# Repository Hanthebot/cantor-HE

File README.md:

# cantor-HE
42 key column staggered split, now with hall effect (WIP)

> Warning! The hardware should work fine, but firmware was not verified yet due to flashing issue.

Hall-effect variant of [Cantor](https://github.com/diepala/cantor), a 42-key split keyboard.

Wooting compatible, reversible, qmk/vial support, and sharing PCB dimension with official Cantor

Firmware / schematics based on [TrueStrike42](https://github.com/byungyoonc/TrueStrike42)

## Preparation

### Board
| Component            | Qty |
| -------------------- | --- |
| PCB                  | 2   |
| SOT-23 SS49E         | 42  |
| SOIC-16 74HC4051(D)  | 6   |
| 0805 0.1uf capacitor | 48  |
| PJ320A TRRS socket   | 2   |
| Blackpill MCU        | 2   |
- For capacitor, 0.1~1uf should be fine
- And obviously, USB-C cable of your choice (with machine) and TRS/TRRS cable of your choice

### Case
- Option A: 3D printed case (I bet you can find one for Cantor)
- Option B: Cheap plate cut
  - requires heat insert and standoff
  - 3T mdf panel of A4 size can fit 2x top & bottom plate
      - and costs about $1
  - plate file provided in this repo
- I do not think original barebone design will work well, as switches are not soldered / mechanically connected.

| Component                  | Qty |
| -------------------------- | --- |
| M2 screw 6mm               | 12  |
| M2 heat insert 3*3         | 12  |
| M2 standoff 7mm + 3mm head | 12  |
- Flathead screw was used
- Standoff can be shorter or longer - but I recommend 5mm at least

### Switches
| Component                          | Qty |
| ---------------------------------- | --- |
| Wooting compatible magnetic switch | 42  |
- While those without side pins should be fine, I'd use one with side pins so that they fix better
- Firmware fix may be required to use the opposite polarity

## [Build guide](GUIDE.md)
WIP. You may check images folder / [Boardloaf-HE's build guide](https://github.com/Hanthebot/Boardloaf-HE/blob/main/GUIDE.md). 

\+ jump back for side detection, firmware is shared between halves

Almost the only difference is that you can solder SOIC-16 multiplexor on either side, preferably at the back of the keyboard.

## Features
- Supports both APC and rapid trigger
- Cheap, simple, and working
- 3 multiplexor on each side, scanning 7 keys per mux

## Changes from Boardloaf-HE
- full duplex communication
- reversible SOIC-16 footprint
- except that, firmware remains largely identical.
- STM32F4x1 MCU, so key precision is expected to have been improved by ~= 10x

## Remarks
- Initial config recommendation: 30% / 20% / 20% / 10% / 10% / 20% (APC act / release; RT init dead / act offset / release offset / bottom dead)
- More documentation: to be done
- Case
  - if your case works for official Cantor, it must work for this
- Random
  - PCB schematics are almost directly from TrueStrike42

## Sponsorship
PCB was generously sponsored by [PCBWay](https://www.pcbway.com/)! Their PCB was indeed of high quality. I did not go with options like matte coating or ENIG, but the board was generally better.

Apart from their great quality, what I felt different was their customer service. There were real human involved in production / communication process and you could feel that they want to help you. In the world filled by chatbot / hallucination, such experience is very rare indeed.

If you are designing a PCB & want some human to check it beforehand, I think PCBWay is superb. They will save you trial and errors.

## Licenses
All code under firmware folder, along with HW, follows GPL v3.
- inherited from TrueStrike42 / Cantor respectively.
- reversible SOT23 / SOIC-16 footprint can be used with MIT.

Webapp follows MIT license.

## Disclaimer
Webapp and firmware (modification) were vibe coded.

Firmware needs future check.

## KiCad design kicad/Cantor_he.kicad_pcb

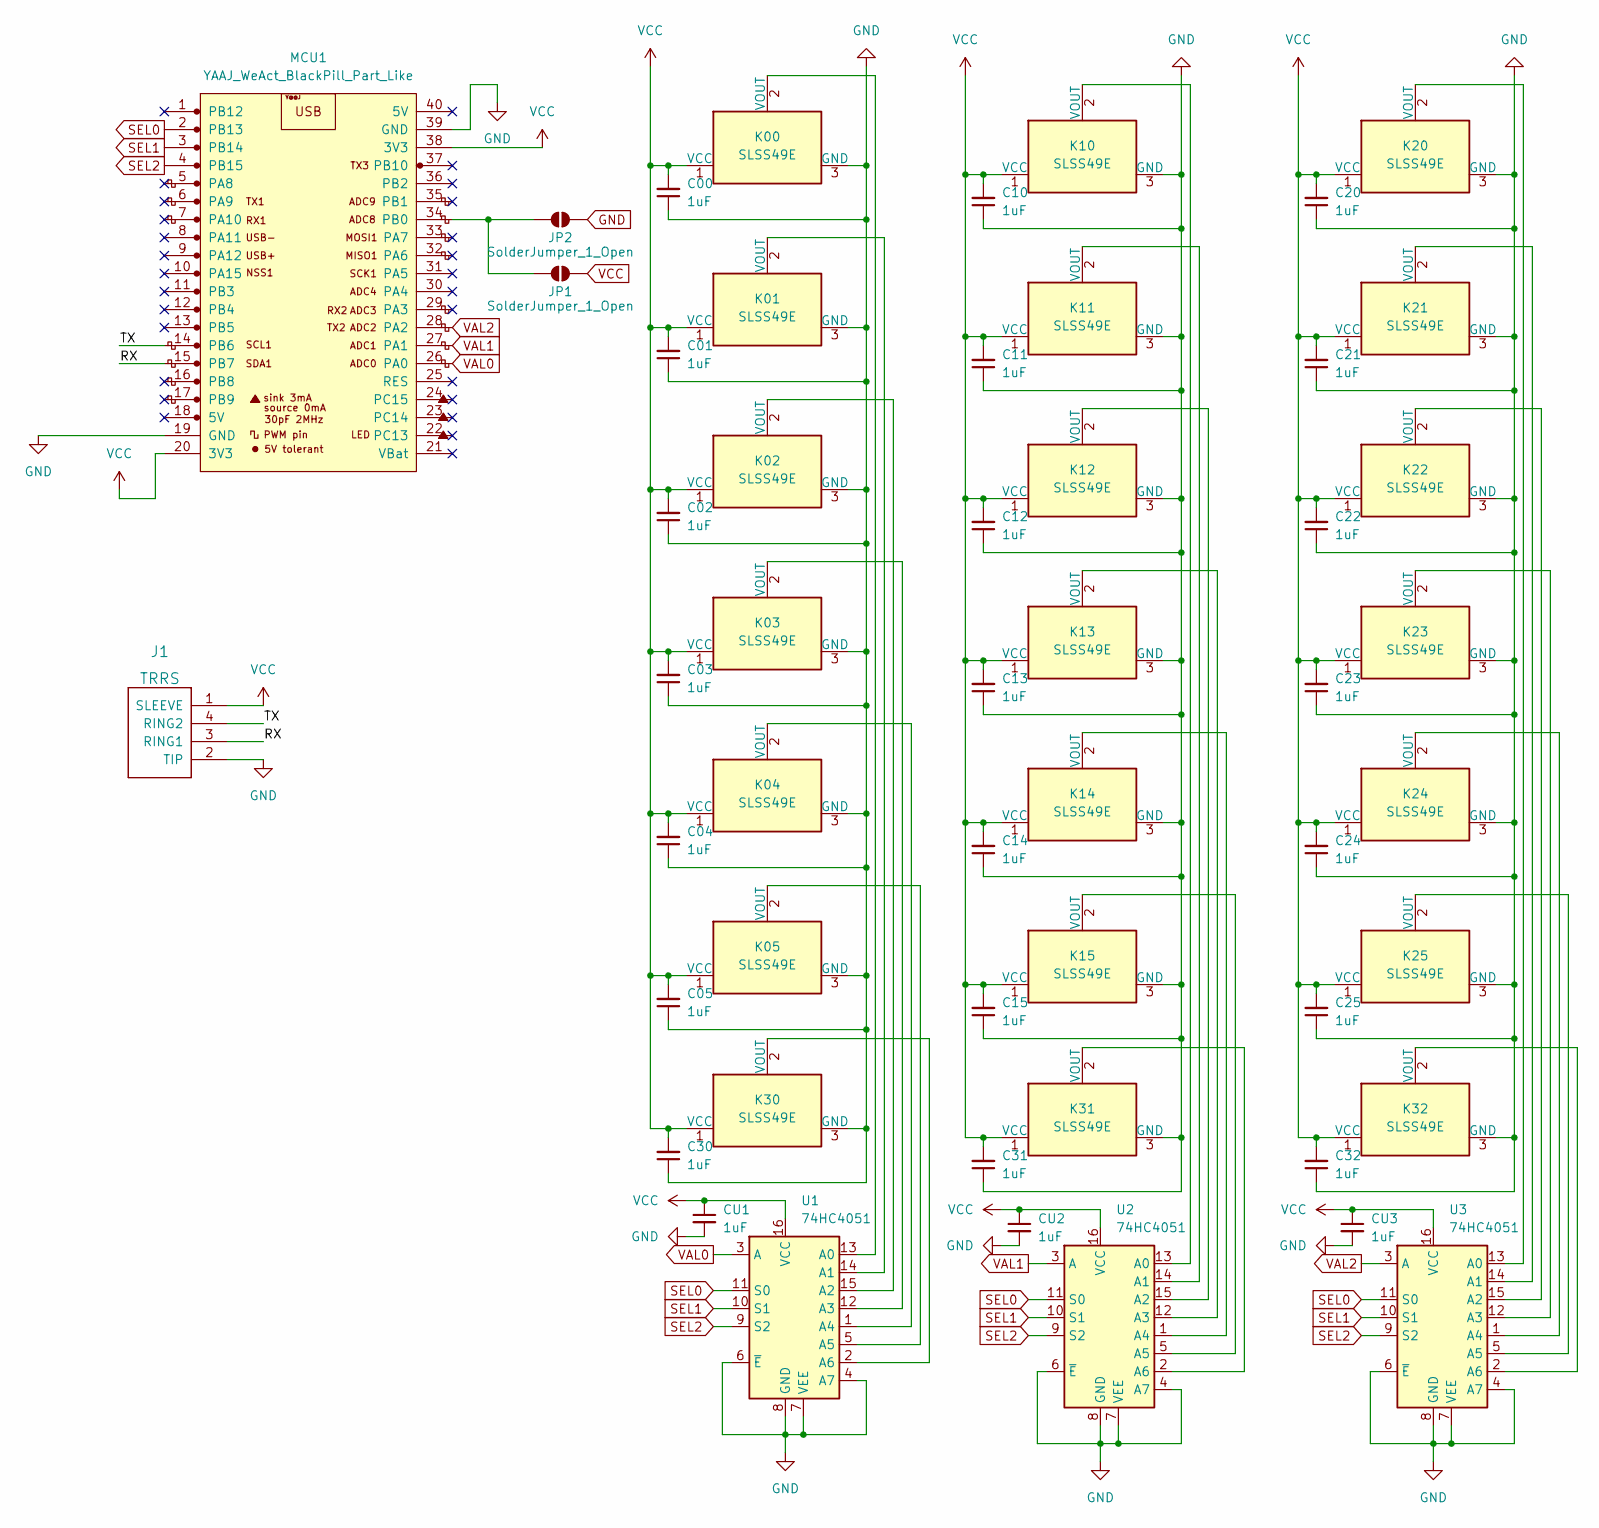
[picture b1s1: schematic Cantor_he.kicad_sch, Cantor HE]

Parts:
C00, C01, C02, C03, C04, C05, C10, C11, C12, C13, C14, C15, C20, C21, C22, C23, C24, C25, C30, C31, C32: 1uF; C_0805_2012Metric_Pad1.18x1.45mm_HandSolder
CU1, CU2, CU3: 1uF; C_0805_2012Metric_Pad1.18x1.45mm_HandSolder
J1: TRRS; MJ-4PP-9_Cantor_MX_TX-RX_Crossover
JP1, JP2: SolderJumper_1_Open; SolderJumper-2_P1.3mm_Open_TrianglePad1.0x1.5mm
K00, K01, K02, K03, K04, K05, K10, K11, K12, K13, K14, K15, K20, K21, K22, K23, K24, K25, K30, K31, K32: SLSS49E; HE-Switch-1U
MCU1: YAAJ_WeAct_BlackPill_Part_Like; Cantor_DS_YAAJ_WeAct_BlackPill_2
U1, U2, U3: 74HC4051; reversible-SOIC-16_3.9x9.9mm_P1.27mm

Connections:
/RX: J1.3 (RING1), MCU1.15 (PB7)
/TX: J1.4 (RING2), MCU1.14 (PB6)
GND: C00.1, C01.1, C02.1, C03.1, C04.1, C05.1, C10.1, C11.1, C12.1, C13.1, C14.1, C15.1, C20.1, C21.1, C22.1, C23.1, C24.1, C25.1, C30.1, C31.1, C32.1, CU1.2, CU2.2, CU3.2, J1.2 (TIP), JP2.2 (B), K00.3 (GND), K01.3 (GND), K02.3 (GND), K03.3 (GND), K04.3 (GND), K05.3 (GND), K10.3 (GND), K11.3 (GND), K12.3 (GND), K13.3 (GND), K14.3 (GND), K15.3 (GND), K20.3 (GND), K21.3 (GND), K22.3 (GND), K23.3 (GND), K24.3 (GND), K25.3 (GND), K30.3 (GND), K31.3 (GND), K32.3 (GND), MCU1.19 (GND), MCU1.39 (GND), U1.4 (A7), U1.6 (~E), U1.7 (VEE), U1.8 (GND), U2.4 (A7), U2.6 (~E), U2.7 (VEE), U2.8 (GND), U3.4 (A7), U3.6 (~E), U3.7 (VEE), U3.8 (GND)
unnamed: JP1.1 (A), JP2.1 (A), MCU1.34 (PB0)
unnamed: K00.2 (VOUT), U1.13 (A0)
unnamed: K01.2 (VOUT), U1.14 (A1)
unnamed: K02.2 (VOUT), U1.15 (A2)
unnamed: K03.2 (VOUT), U1.12 (A3)
unnamed: K04.2 (VOUT), U1.1 (A4)
unnamed: K05.2 (VOUT), U1.5 (A5)
unnamed: K10.2 (VOUT), U2.13 (A0)
unnamed: K11.2 (VOUT), U2.14 (A1)
unnamed: K12.2 (VOUT), U2.15 (A2)
unnamed: K13.2 (VOUT), U2.12 (A3)
unnamed: K14.2 (VOUT), U2.1 (A4)
unnamed: K15.2 (VOUT), U2.5 (A5)
unnamed: K20.2 (VOUT), U3.13 (A0)
unnamed: K21.2 (VOUT), U3.14 (A1)
unnamed: K22.2 (VOUT), U3.15 (A2)
unnamed: K23.2 (VOUT), U3.12 (A3)
unnamed: K24.2 (VOUT), U3.1 (A4)
unnamed: K25.2 (VOUT), U3.5 (A5)
unnamed: K30.2 (VOUT), U1.2 (A6)
unnamed: K31.2 (VOUT), U2.2 (A6)
unnamed: K32.2 (VOUT), U3.2 (A6)
SEL0: MCU1.2 (PB13), U1.11 (S0), U2.11 (S0), U3.11 (S0)
SEL1: MCU1.3 (PB14), U1.10 (S1), U2.10 (S1), U3.10 (S1)
SEL2: MCU1.4 (PB15), U1.9 (S2), U2.9 (S2), U3.9 (S2)
VAL0: MCU1.26 (PA0), U1.3 (A)
VAL1: MCU1.27 (PA1), U2.3 (A)
VAL2: MCU1.28 (PA2), U3.3 (A)
VCC: C00.2, C01.2, C02.2, C03.2, C04.2, C05.2, C10.2, C11.2, C12.2, C13.2, C14.2, C15.2, C20.2, C21.2, C22.2, C23.2, C24.2, C25.2, C30.2, C31.2, C32.2, CU1.1, CU2.1, CU3.1, J1.1 (SLEEVE), JP1.2 (B), K00.1 (VCC), K01.1 (VCC), K02.1 (VCC), K03.1 (VCC), K04.1 (VCC), K05.1 (VCC), K10.1 (VCC), K11.1 (VCC), K12.1 (VCC), K13.1 (VCC), K14.1 (VCC), K15.1 (VCC), K20.1 (VCC), K21.1 (VCC), K22.1 (VCC), K23.1 (VCC), K24.1 (VCC), K25.1 (VCC), K30.1 (VCC), K31.1 (VCC), K32.1 (VCC), MCU1.20 (3V3), MCU1.38 (3V3), U1.16 (VCC), U2.16 (VCC), U3.16 (VCC)

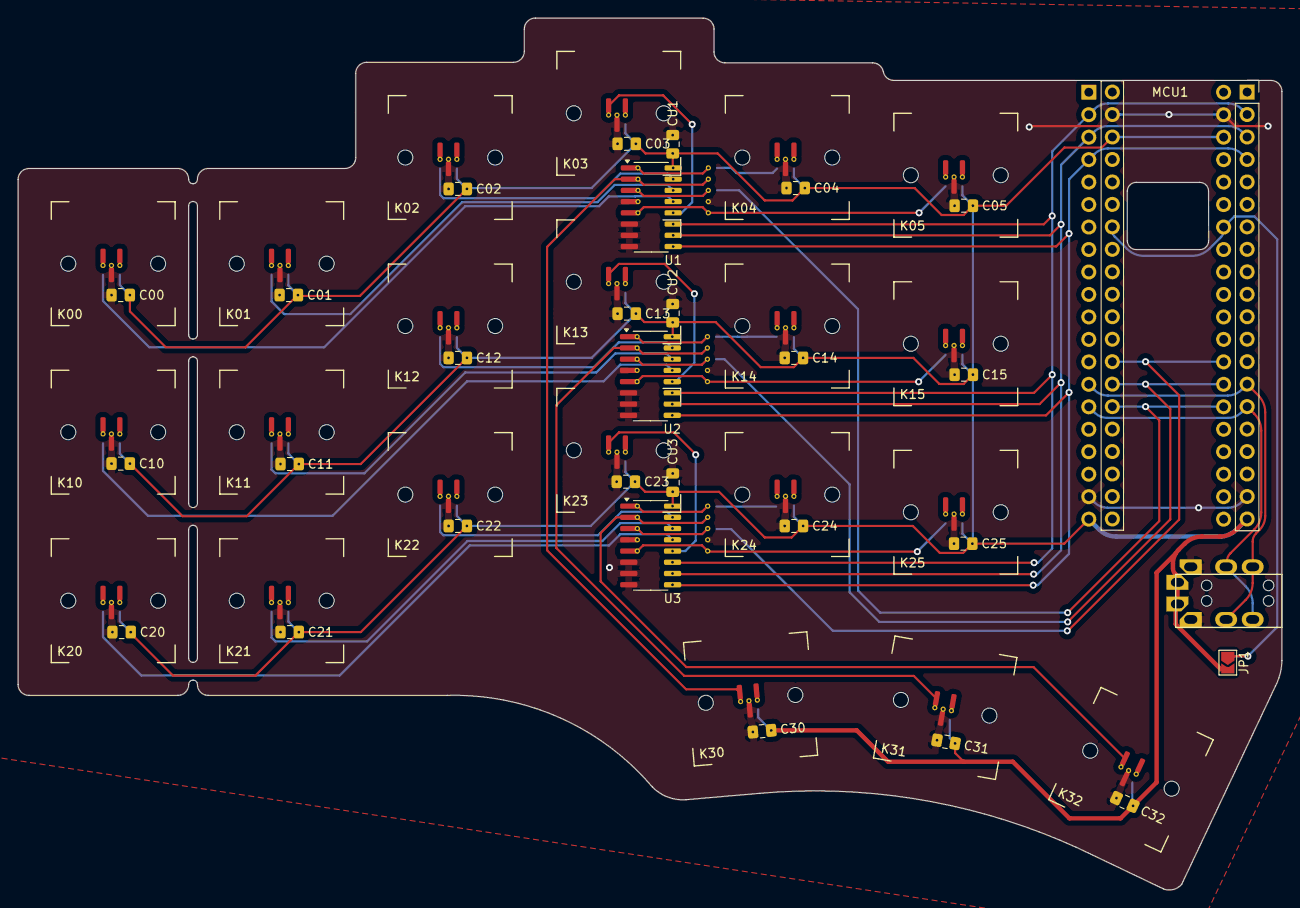
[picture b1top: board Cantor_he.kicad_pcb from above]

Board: 2 copper layers, 142.9 x 98.6 mm, 52 parts (1 on the bottom side), 32 nets.
